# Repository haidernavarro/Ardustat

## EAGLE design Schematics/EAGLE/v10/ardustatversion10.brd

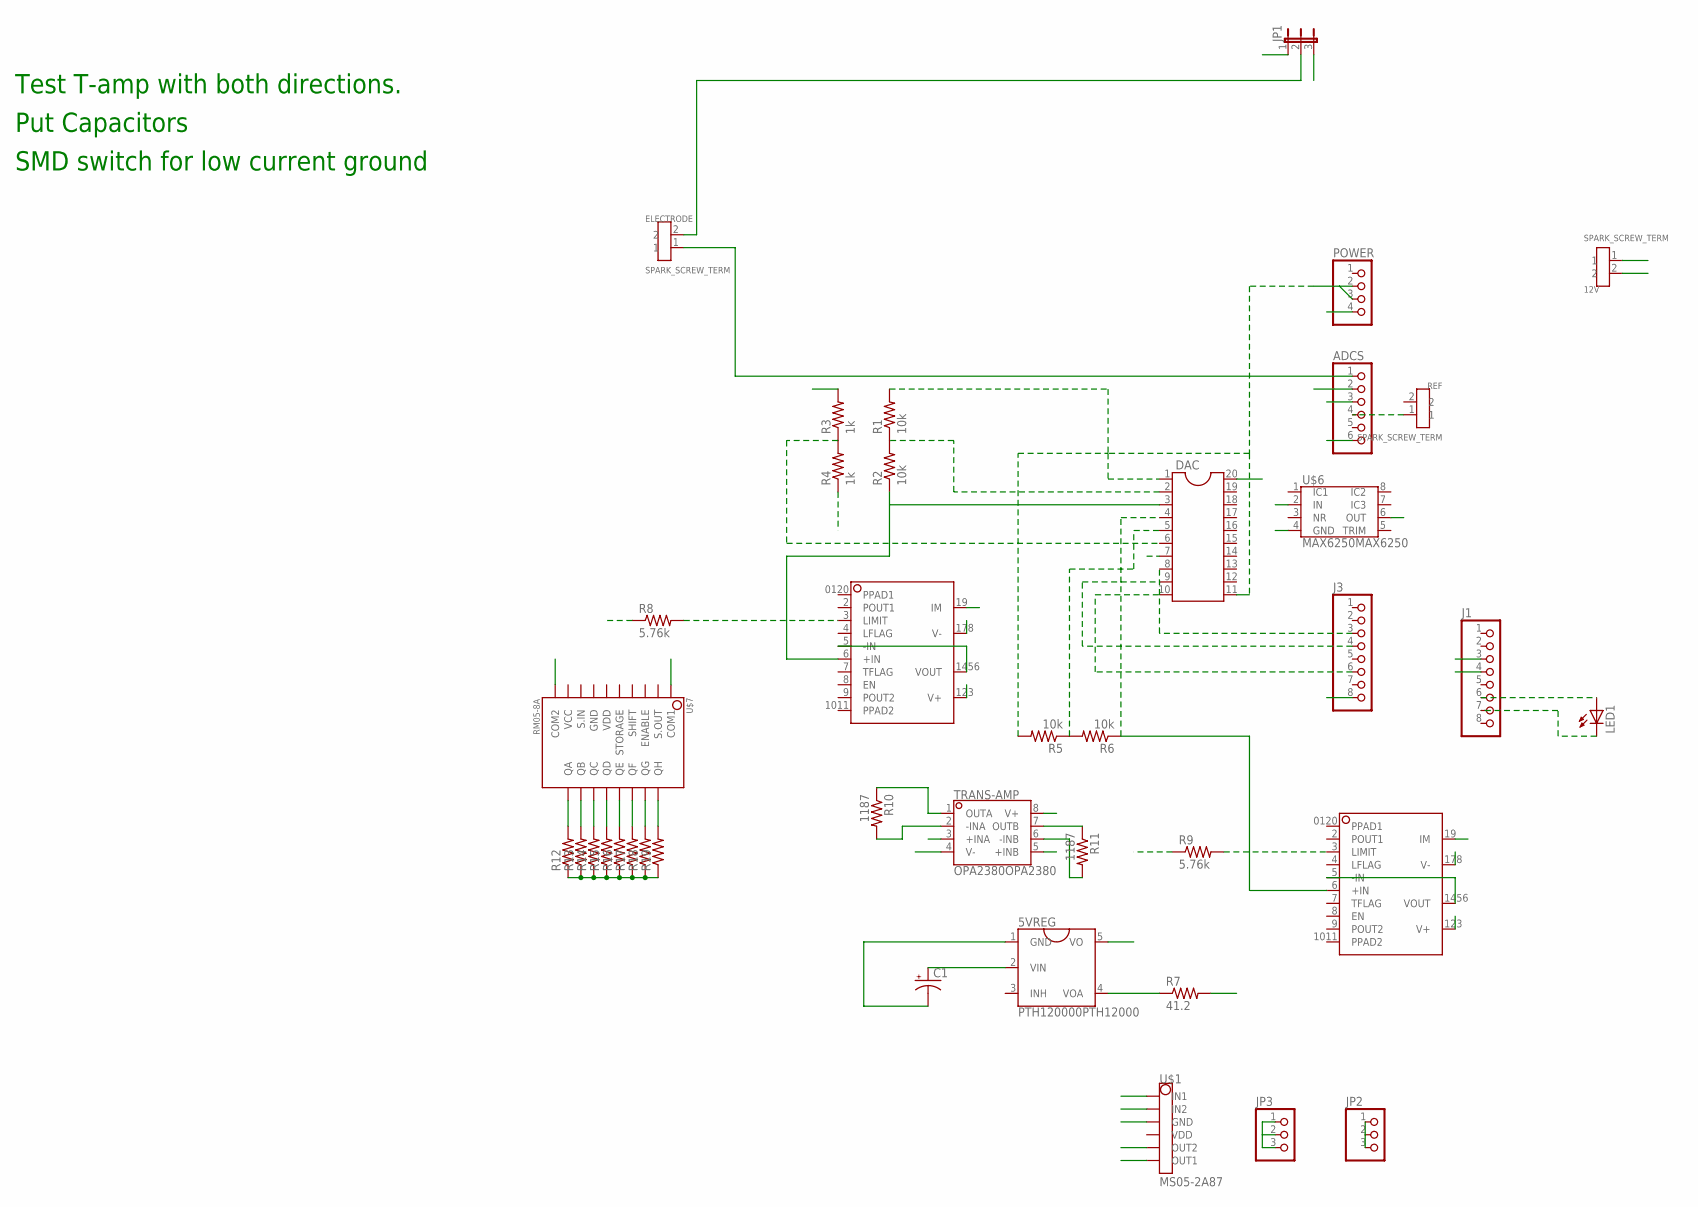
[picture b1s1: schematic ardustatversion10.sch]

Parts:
5VREG: PTH120000PTH12000; PTH120000
12V: SPARK_SCREW_TERM
ADCS: PINHD-1X6; 1X06
C1: CPOL-USE5-10.5; E5-10,5
DAC: DIL20S; SOCKED-20
ELECTRODE: SPARK_SCREW_TERM
J1, J3: PINHD-1X8; 1X08
JP1: JP2E; JP2
JP2, JP3: PINHD-1X3; 1X03
LED1: LED5MM
POWER: PINHD-1X4; 1X04
R1, R2, R5, R6: 10k; R1206
R3, R4: 1k; R1206
R7: 41.2; M1206
R8: 5.76k; R1206
R9: 5.76k; M1206
R10, R11: 1187; M1206
R12, R13, R14, R15, R16, R17, R18, R19: R-US_0207/12; 0207/12
REF: SPARK_SCREW_TERM
TRANS-AMP: OPA2380OPA2380; OPA2380
U$1: MS05-2A87
U$3, U$4: OPA569OPA569; OPA569
U$6: MAX6250MAX6250; MAX6250
U$7: RM05-8A

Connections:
GND: 5VREG.1 (GND), 12V.2, C1.-, DAC.1, DAC.11, JP1.3, POWER.2, POWER.3, R1.2, R4.1, R5.2, R7.2, R8.1, R9.1, TRANS-AMP.4 (V-), U$1.P$3 (GND), U$3.178 (V-), U$4.178 (V-), U$6.4 (GND)
unnamed: DAC.6, R3.1, R4.2
unnamed: DAC.10, J3.6
unnamed: DAC.9, J3.4
unnamed: DAC.8, J3.3
unnamed: DAC.7, J1.3
unnamed: DAC.2, R1.1, R2.2
unnamed: ADCS.1, ELECTRODE.1, JP2.1, JP2.2, JP2.3, R12.1, R13.1, R14.1, R15.1, R16.1, R17.1, R18.1, R19.1
unnamed: U$1.P$2 (IN2), U$4.5 (-IN), U$4.1456 (VOUT)
unnamed: R10.2, TRANS-AMP.2 (-INA), U$3.19 (IM)
unnamed: R12.2, U$7.P$11 (QA)
unnamed: DAC.5, R5.1, R6.2
unnamed: R8.2, U$3.3 (LIMIT)
unnamed: R10.1, TRANS-AMP.1 (OUTA)
unnamed: ADCS.2, DAC.3, R2.1, U$3.6 (+IN), U$7.P$1 (COM1), U$7.P$10 (COM2)
unnamed: R9.2, U$4.3 (LIMIT)
unnamed: J1.6, LED1.A
unnamed: J1.7, LED1.K (C)
unnamed: 5VREG.5 (VO), DAC.20, TRANS-AMP.8 (V+), U$3.123 (V+), U$4.123 (V+)
unnamed: ADCS.4, REF.1
unnamed: ADCS.3, ELECTRODE.2, JP1.2
unnamed: 5VREG.2 (VIN), 12V.1, C1.+, POWER.4, U$6.2 (IN)
unnamed: JP3.1, JP3.2, JP3.3, U$1.P$6 (OUT1)
unnamed: J3.8, R3.2, TRANS-AMP.3 (+INA), TRANS-AMP.5 (+INB), U$6.6 (OUT)
unnamed: 5VREG.4 (VOA), R7.1
unnamed: U$1.P$1 (IN1), U$3.5 (-IN), U$3.1456 (VOUT)
unnamed: R13.2, U$7.P$12 (QB)
unnamed: R14.2, U$7.P$13 (QC)
unnamed: R15.2, U$7.P$14 (QD)
unnamed: R16.2, U$7.P$15 (QE)
unnamed: DAC.4, R6.1, U$4.6 (+IN)
unnamed: R17.2, U$7.P$16 (QF)
unnamed: R18.2, U$7.P$17 (QG)
unnamed: R19.2, U$7.P$18 (QH)
unnamed: JP1.1, U$1.P$5 (OUT2)
unnamed: ADCS.6, R11.1, TRANS-AMP.7 (OUTB)
unnamed: R11.2, TRANS-AMP.6 (-INB), U$4.19 (IM)

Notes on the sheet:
Test T-amp with both directions.
Put Capacitors
SMD switch for low current ground

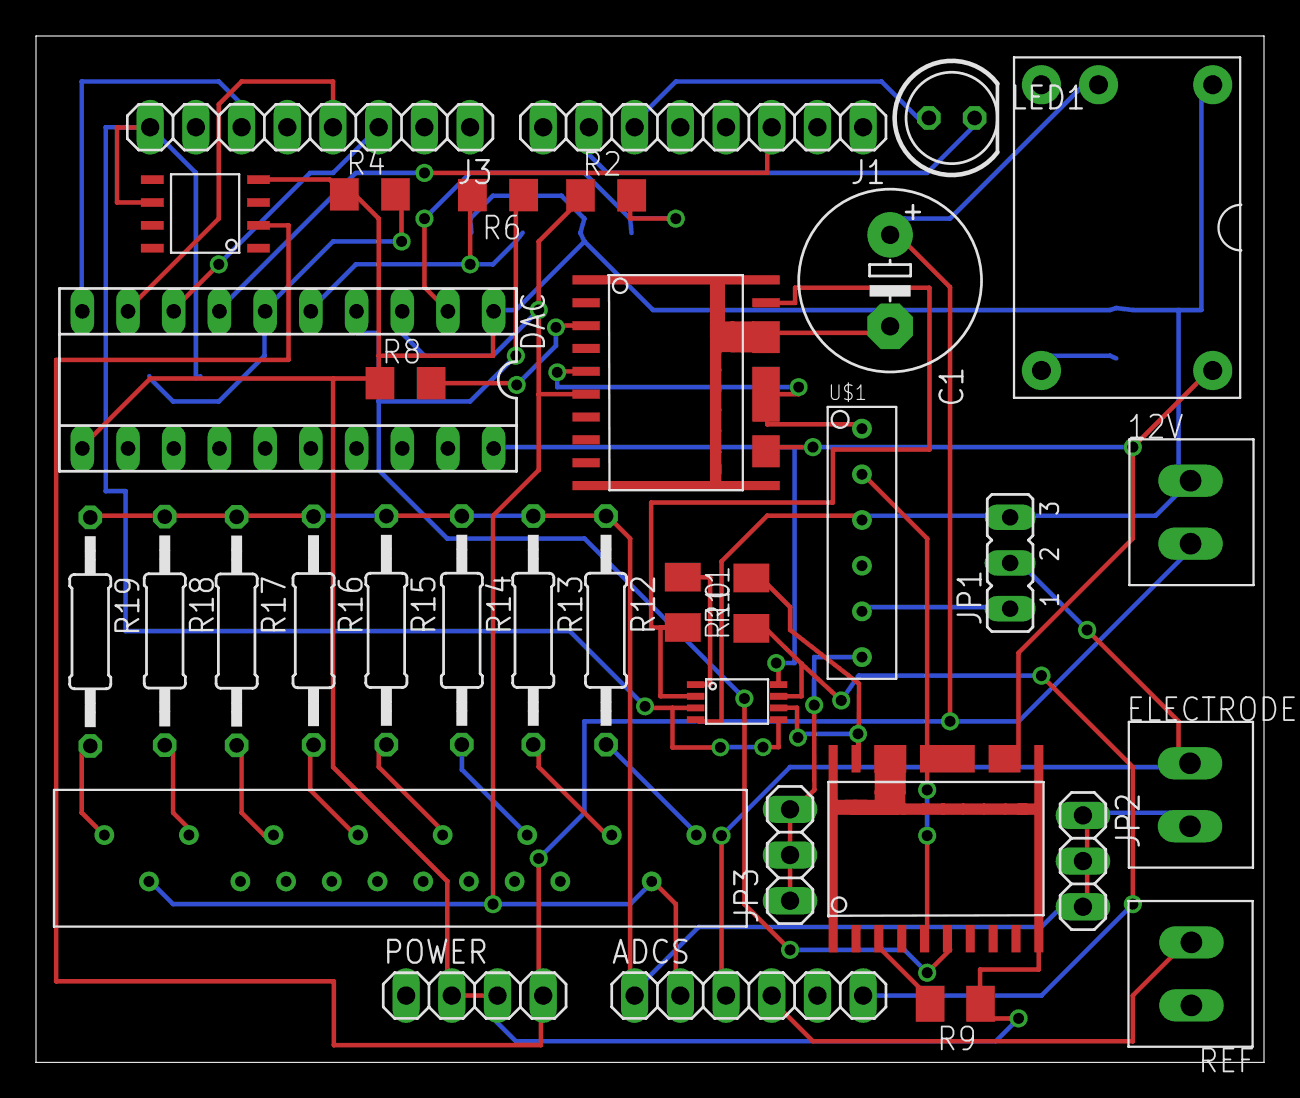
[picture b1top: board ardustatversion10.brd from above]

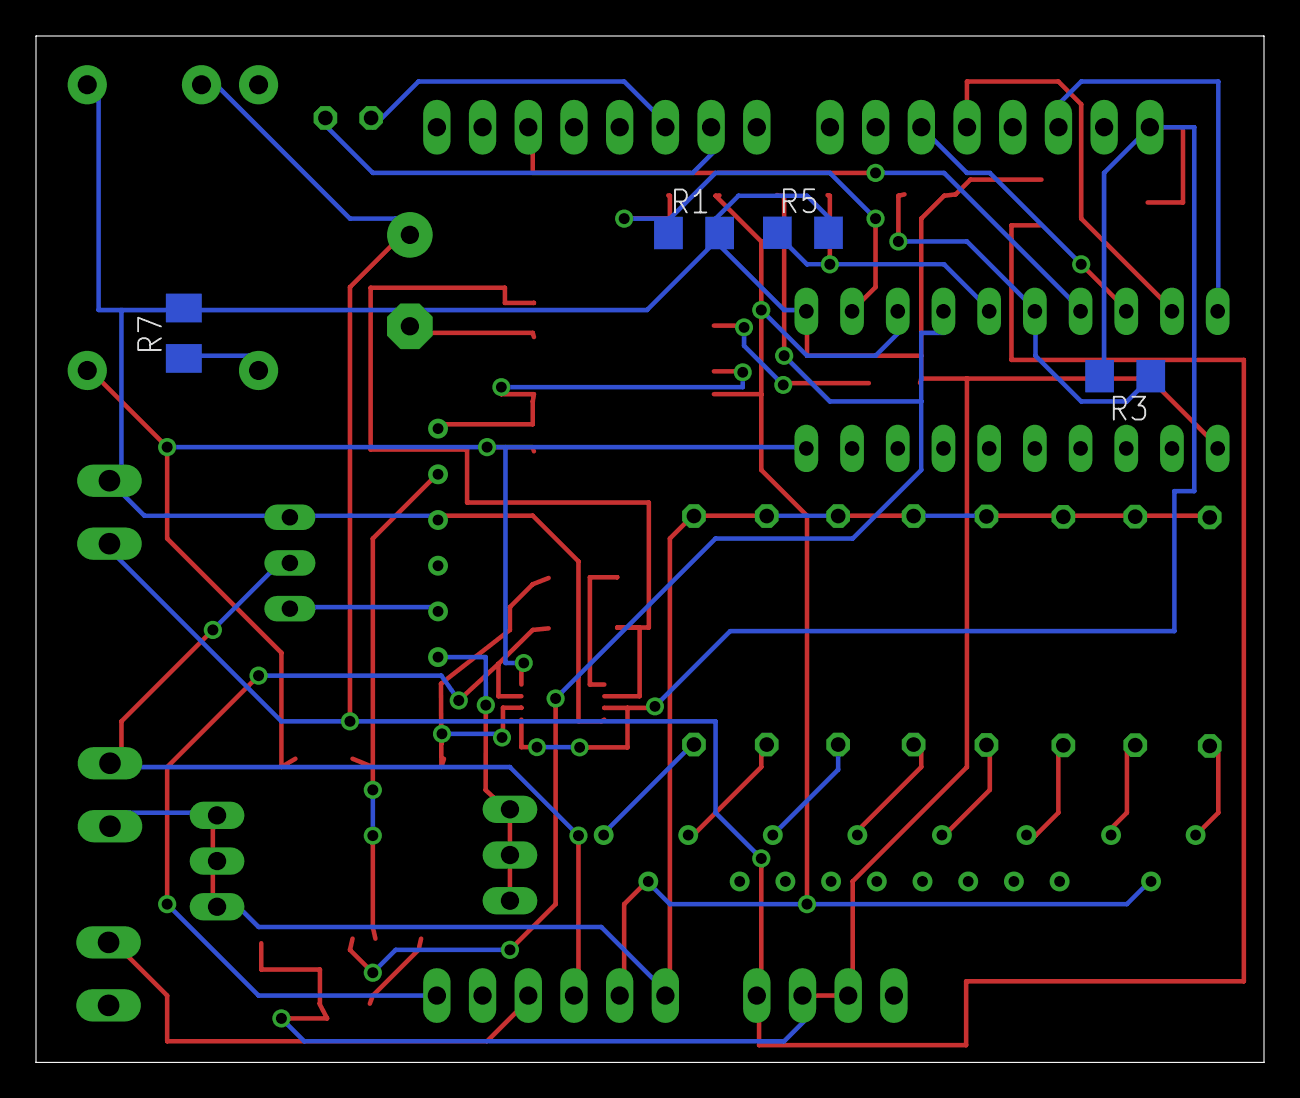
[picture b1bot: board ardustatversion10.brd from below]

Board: 2 copper layers, 68.2 x 57.0 mm, 39 parts (4 on the bottom side), 37 nets.

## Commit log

2012-03-06 packges
2012-06-12 added script to make nodejs work under linux
2012-06-18 Removed deprecated code & moved files
2012-06-18 Improved startardustat script
2012-06-18 Fixed .gitignore
2012-06-18 Removed deprecated firmware
2012-06-18 Removed deprecated schematics
2012-06-18 Fixed readme instructions
2012-06-18 Fixed readme more
2012-06-18 high/low current switching
2012-06-18 fixed misspelling
2012-06-18 Fixed bug in startardustat for macs
2012-06-18 changed current plotter
2012-06-18 Fixed graphing for high/low current switch
2012-06-18 Added messages for current mode switching
2012-06-18 Added batch script to simplify node install on Windows
2012-06-18 Firmware low current update
2012-06-18 Split up functions for high/low current galv
2012-06-18 Added dummy resistance value for high current galv
2012-06-18 New firmware
2012-06-18 Manually copied high_current_stuff files to master
2012-06-18 Fixed negative high current bug
2012-06-18 Removed blink from galvanostat functions
2012-06-19 Cleaned up functions.js
2012-06-19 Cleaned up html files
2012-06-19 Misc expressserver improvements
2012-06-19 Logging
2012-06-19 Removed annoying console.log of all logged data
2012-06-19 Changed back logging code
2012-06-19 Added mongo daemon to startardustat
2012-06-19 Updated gitignore
2012-06-21 Improved logging interface
2012-06-21 Improved startup script
2012-06-21 Fixed config file to first run
2012-06-21 Fixed startup script
2012-06-26 Reverted to old version of express library since new one broke code
2012-06-26 Fixed Ardustat_Viewer libraries
2012-06-26 Improved code for cycler
2012-06-26 Graphical cycler interface; saved cycling parameters are broken though
2012-06-27 Comments, CSS, no cycler page, readme
2012-06-27 negative resistance calibration fix hack
2012-06-27 Moved some debug functionality to index page; code cleanup; other improvements
2012-06-27 Changed cycling interface
2012-06-27 Moved functionality back to separate pages
2012-06-27 Fixed bug with potentiostat when cycling
2012-06-27 Added remove button for cycling
2012-06-28 Reverted to old calibration code
2012-06-28 Put back calibration fix
2012-06-28 Fix for bug with charging galv and null cutoff_voltage
2012-06-28 Moved Ardustat_Viewer code to Ardustat_Control. CV viewer still broken.
2012-06-28 Re-fixed null cutoff_potential bug; readme
2012-06-28 Fixed startup scripts to reflect that there is no Ardustat_Viewer anymore
2012-06-28 Folder renaming; file moving; centered graph titles
2012-06-28 Removed outdated firmware
2012-06-28 Fixed readme
2012-06-28 Slowed default serial port command sending rate
2012-06-28 Added some info; removed firstRun.bat
2012-06-29 Added Export CSV button on plotter page; removed exportData.sh script
2012-06-29 Windows support for export CSV function
2012-06-29 Added support for starting cycler with saved settings
2012-06-29 Removed unneccessary console.log()'s
2012-06-29 Added filename notification for export csv button
2012-07-09 HTML layout
2012-07-09 Automatically move ground to 0 before calibration
2012-07-09 Fixed bug with moving ground in calibration
2012-07-09 Removed moveground line from calibration
2012-07-09 Remove old calibration file before recalibration
2012-07-10 Added mac app
2012-07-10 Improved startup script so it installs dependencies automatically
2012-07-10 Fixed calibration bug with deleting old calibration file
2012-07-10 Added debugging message for calibration
2012-07-10 More calibration debugging
2012-07-10 Moved startArdustat.sh script and updated readme
2012-07-10 Moved startArdustat.sh back out of Software since it broke Platypus app
2012-07-10 Automatically upload firmware on mac/linux
2012-07-10 Fixed avrdude install bug & updated readme
2012-07-11 Removed some of the automatic stuff from startArdustat.sh
2012-07-11 Removed check in startardustat for homebrew
2012-07-11 Fixed mongodb install on mac
2012-07-11 Added 'upload firmware' button and page
2012-07-11 Moved upload firmware button to debug page
2012-07-11 Fixed bug with commands being sent improperly
2012-07-12 Fixed blink function
2012-07-12 Added check for 5 chars before sending command
2012-07-12 Added another app for installing dependencies
2012-07-12 Fixed permissions
2012-07-12 Added new ardustat.lbr
2012-07-12 Added rigers' new schematic
2012-07-12 Changes to convenience scripts
2012-07-12 Updated fileinfo
2012-07-12 Switched from FFI to execSync libraries for execution
2012-07-12 Added button to check if firmware is loaded
2012-07-16 Added specific version of serialport since new version broke code
2012-07-16 Removed unneccessary newline from last commit
2012-07-16 Moved software into folders for different OS's
2012-07-16 Moved avrdude software out of Firmware folder
2012-07-16 Changed startArdustat scripts add added node_modules for Linux
2012-07-16 Added node_modules for mac
2012-07-16 Added mac startArdustat script
2012-07-16 Added node_modules for Windows
2012-07-16 Removed execSync dependency & added startArdustat script for linux
2012-07-17 Removed symlinks from mac app
2012-07-17 Changed method of uploading firmware for Windows compatibility
2012-07-17 Fixed mac installer app
2012-07-17 Removed libraries from Windows
2012-07-17 Added compiled node.js binary on mac
2012-07-17 Added mongodb binaries to Ardustat.app
2012-07-17 Changed license to GPLV2 & fixed check_firmware() on Mac
2012-07-17 Moved mongodb directory to ~/Library/Application Support
2012-07-17 Added avrdude binary to mac app
2012-07-17 Removed OS check in connectToSerial()
2012-07-19 Fixed directory for mongoexport on mac
2012-07-19 Fixed missing newline in read me
2012-07-19 Removed unnecessary mongoDB files
2012-07-23 Added resistance override button to debug page
2012-07-23 Made calibration files be created outside of mac app
2012-07-23 Better navigation between pages on website
2012-07-23 Moved navigation links to top of pages
2012-07-23 Fixed annoying mkdir errors
2012-07-24 Removed .gitignore file
2012-07-24 Better start script compatibility for FTDI arduinos
2012-07-24 Better start script compatibility for FTDI arduinos - linux
2012-07-24 Updated galvanostat functions for custom resistance override
2012-07-24 Added missing close brackets
2012-07-24 Added switch and moved some wires
2012-09-04 V9 part list
2012-09-05 Updated ardustat Eagle library
2012-09-05 Almost finished V10 board schematic
